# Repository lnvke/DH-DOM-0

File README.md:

# navball
A compact display showing horizon, heading, and ground speed. Makes use of the BMI270 inertial measuring unit (IMU) to provide orientation, velocity, and acceleration data to display on screen.

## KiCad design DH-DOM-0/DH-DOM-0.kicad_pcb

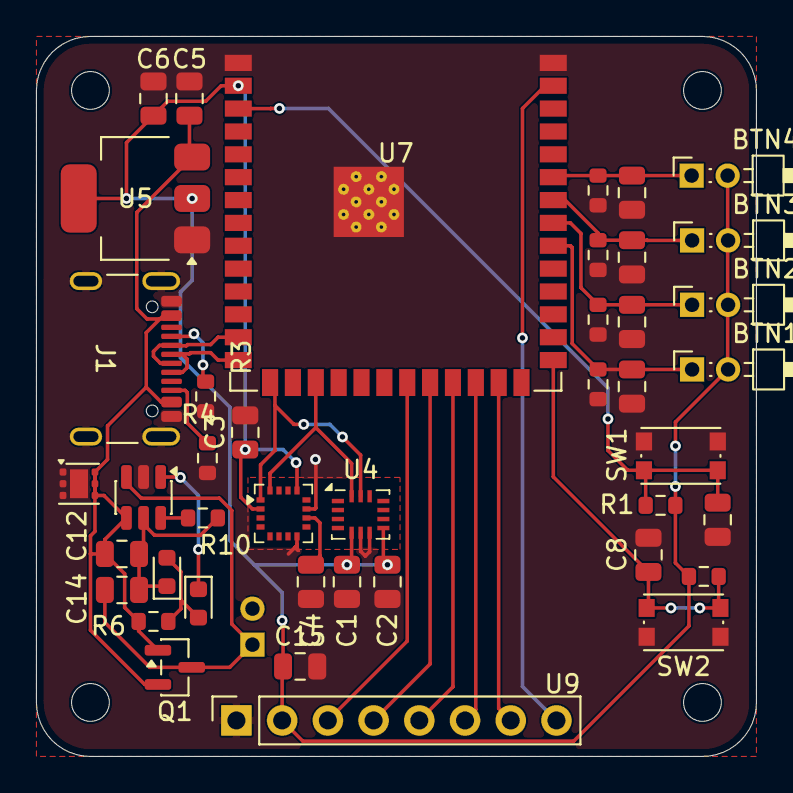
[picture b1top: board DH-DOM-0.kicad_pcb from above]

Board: 2 copper layers, 40.0 x 40.0 mm, 47 parts (1 on the bottom side), 27 nets.

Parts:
BTN1, BTN2, BTN3, BTN4: SW_Push; PinHeader_2x01_P2.00mm_Horizontal
C1, C2, C3, C7, C8, C9, C10, C11, C13, C15: 100n; C_0805_2012Metric
C4, C5, C6, C12: 10u; C_0805_2012Metric
C14: 4.7u; C_0805_2012Metric
D1, D2: LED; LED_0603_1608Metric
J1: USB_C_Receptacle_USB2.0_14P; USB_C_Receptacle_GCT_USB4105-xx-A_16P_TopMnt_Horizontal
J2: Conn_01x02; PinHeader_2x01_P2.00mm_Vertical
MH1, MH2, MH3, MH4: MountingHole_2.1mm
Q1: FDN340P; SOT-23
R1, R2: 1K; R_0603_1608Metric
R3, R4: 5.1k; R_0603_1608Metric
R5, R7, R8, R9: 10k; R_0603_1608Metric
R6: 1k; R_0603_1608Metric
R10: 10K; R_0603_1608Metric
SW1: RST; SW_Push_1P1T_NO_CK_KMR2
SW2: BOOT; SW_Push_1P1T_NO_CK_KMR2
U3: MMC5983MA; LGA-16_3x3mm_P0.5mm
U4: BMI270; Bosch_LGA-14_3x2.5mm_P0.5mm
U5: NCP1117-3.3_SOT223; SOT-223-3_TabPin2
U6: TVS1400DRV; WSON-6-1EP_2x2mm_P0.65mm_EP1x1.6mm
U7: ESP32-S3-WROOM-1-N4R8; ESP32-S3-WROOM-1
U8: TP4057; TSOT-23-6
U9: ST7789; PinSocket_1x08_P2.54mm_Vertical

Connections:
+3V3: BTN1.2, BTN2.2, BTN3.2, BTN4.2, C1.1, C2.1, C3.1, C6.1, C15.1, R1.1, R2.1, U3.2 (VDD), U3.13 (VDDIO), U4.5 (VDDI0), U4.8 (VDD), U5.2 (VO), U7.2 (3V3), U9.2
+5V: C5.1, C12.1, J1.A4 (VBUS), J1.A9 (VBUS), J1.B4 (VBUS), J1.B9 (VBUS), Q1.1 (G), Q1.2 (S), R6.2, U5.3 (VI), U6.4 (IN), U6.5 (IN), U6.6 (IN), U8.4 (V_{CC})
/BACKLIGHT: U7.39 (IO1), U9.8
/BAT+: C14.1, J2.1, Q1.3 (D), U8.3 (BAT)
/BTN1: BTN1.1, C9.1, R5.1, U7.32 (IO39)
/BTN2: BTN2.1, C10.1, R7.1, U7.33 (IO40)
/BTN3: BTN3.1, C11.1, R8.1, U7.34 (IO41)
/BTN4: BTN4.1, C13.1, R9.1, U7.35 (IO42)
/D+: J1.A6 (D+), J1.B6 (D+), U7.14 (USB_D+)
/D-: J1.A7 (D-), J1.B7 (D-), U7.13 (USB_D-)
/D/C: U7.24 (IO47), U9.6
/MOSI: U7.22 (IO14), U9.4
/RESET: U7.23 (IO21), U9.5
/SCL: U3.1 (SCx), U4.13 (SCx), U7.15 (IO3)
/SCLK: U7.21 (IO13), U9.3
/SDA: U3.16 (MOSI/SDA), U4.14 (SDx), U7.17 (IO9)
/SS: U7.25 (IO48), U9.7
GND: C1.2, C2.2, C3.2, C4.2, C5.2, C6.2, C7.2, C8.2, C9.2, C10.2, C11.2, C13.2, C15.2, J1.A1 (GND), J1.A12 (GND), J1.B1 (GND), J1.B12 (GND), J1.SH (SHIELD), J2.2, R3.2, R4.2, R5.2, R7.2, R8.2, R9.2, SW1.1, SW2.1, U3.8 (GND), U3.11 (GND), U4.6 (GNDI0), U4.7 (GND), U5.1 (GND), U6.1 (GND), U6.2 (GND), U6.3 (GND), U6.7 (GND), U7.1 (GND), U7.40 (GND), U7.41 (GND), U8.2 (GND), U9.1
unnamed: D1.2 (A), D2.2 (A), R6.1
unnamed: C12.2, C14.2, D1.1 (K), R10.2, U8.5 (STDBY)
unnamed: D2.1 (K), U8.1 (~CHRG)
unnamed: J1.A5 (CC1), R3.1
unnamed: J1.B5 (CC2), R4.1
unnamed: C4.1, U3.10 (CAP)
unnamed: C7.1, R1.2, SW1.2, U7.3 (EN)
unnamed: C8.1, R2.2, SW2.2, U7.27 (IO0)
unnamed: R10.1, U8.6 (PROG)

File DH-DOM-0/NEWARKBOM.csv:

"Reference","Qty","Value","DNP","Exclude from BOM","Exclude from Board","Footprint","Datasheet"
"BTN1,BTN2,BTN3,BTN4","4","SW_Push","","","","Connector_PinHeader_2.00mm:PinHeader_2x01_P2.00mm_Horizontal",""
"C1,C2,C3,C7,C8,C9,C10,C11,C13,C14","10","100n","","","","Capacitor_SMD:C_0805_2012Metric",""
"C4,C5,C6,C12","4","10u","","","","Capacitor_SMD:C_0805_2012Metric",""
"C15","1","4.7u","","","","Capacitor_SMD:C_0805_2012Metric",""
"D1,D2","2","LED","","","","LED_SMD:LED_0603_1608Metric",""
"J1","1","USB_C_Receptacle_USB2.0_14P","","","","Connector_USB:USB_C_Receptacle_GCT_USB4105-xx-A_16P_TopMnt_Horizontal","https://www.usb.org/sites/default/files/documents/usb_type-c.zip"
"J2","1","Conn_01x02","","","","Connector_PinHeader_2.00mm:PinHeader_2x01_P2.00mm_Vertical",""
"Q1","1","FDN340P","","","","Package_TO_SOT_SMD:SOT-23","https://www.onsemi.com/pub/Collateral/FDN340P-D.PDF"
"R1,R2","2","1K","","","","Resistor_SMD:R_0603_1608Metric",""
"R3,R4","2","5.1k","","","","Resistor_SMD:R_0603_1608Metric",""
"R5,R7,R8,R9","4","10k","","","","Resistor_SMD:R_0603_1608Metric",""
"R6","1","1k","","","","Resistor_SMD:R_0603_1608Metric",""
"R10","1","10K","","","","Resistor_SMD:R_0603_1608Metric",""
"SW1","1","RST","","","","Button_Switch_SMD:SW_Push_1P1T_NO_CK_KMR2",""
"SW2","1","BOOT","","","","Button_Switch_SMD:SW_Push_1P1T_NO_CK_KMR2",""
"U3","1","MMC5983MA","","","","Package_LGA:LGA-16_3x3mm_P0.5mm",""
"U4","1","BMI270","","","","Package_LGA:Bosch_LGA-14_3x2.5mm_P0.5mm","https://www.bosch-sensortec.com/media/boschsensortec/downloa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"
"U5","1","NCP1117-3.3_SOT223","","","","Package_TO_SOT_SMD:SOT-223-3_TabPin2","http://www.onsemi.com/pub_link/Collateral/NCP1117-D.PDF"
"U6","1","TVS1400DRV","","","","Package_SON:WSON-6-1EP_2x2mm_P0.65mm_EP1x1.6mm","http://www.ti.com/lit/ds/symlink/tvs1400.pdf"
"U7","1","ESP32-S3-WROOM-1-N4R8","","","","RF_Module:ESP32-S3-WROOM-1","https://www.espressif.com/sites/default/files/documentation/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"
"U8","1","TP4057","","","","Package_TO_SOT_SMD:TSOT-23-6","http://toppwr.com/uploadfile/file/20230304/640302a47b738.pdf"
"U9","1","ST7789","","","","Connector_PinSocket_2.54mm:PinSocket_1x08_P2.54mm_Vertical",""

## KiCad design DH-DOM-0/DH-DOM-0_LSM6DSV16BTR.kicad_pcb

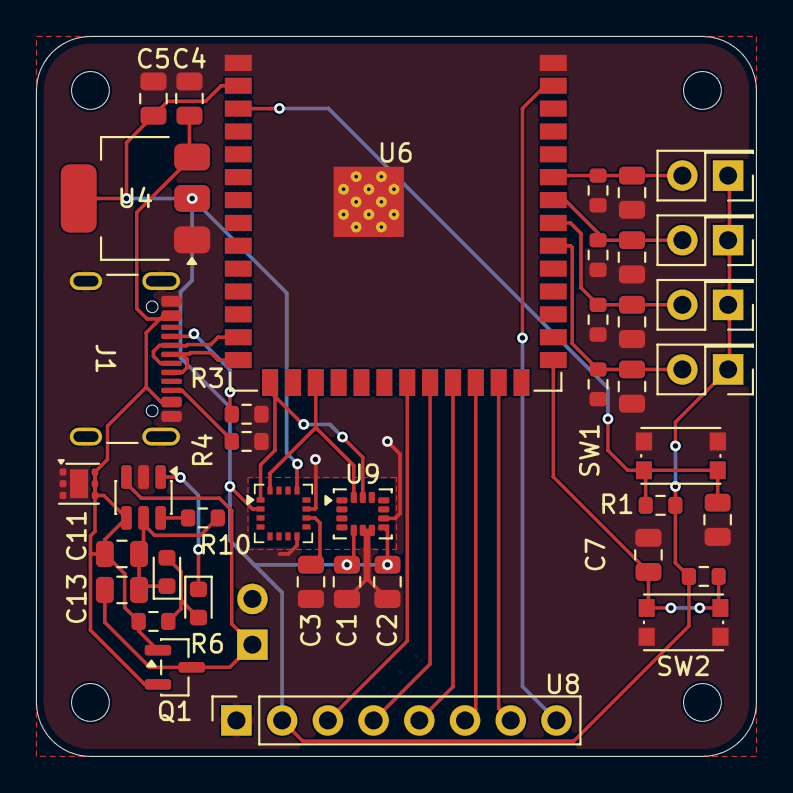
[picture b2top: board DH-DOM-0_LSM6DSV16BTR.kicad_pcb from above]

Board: 2 copper layers, 40.0 x 40.0 mm, 45 parts (1 on the bottom side), 27 nets.

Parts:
BTN1, BTN2, BTN3, BTN4: SW_Push; PinHeader_2x01_P2.54mm_Vertical
C1, C2, C6, C7, C8, C9, C10, C12: 100n; C_0805_2012Metric
C3, C4, C5, C11: 10u; C_0805_2012Metric
C13: 4.7u; C_0805_2012Metric
D1, D2: LED; LED_0603_1608Metric
J1: USB_C_Receptacle_USB2.0_14P; USB_C_Receptacle_GCT_USB4105-xx-A_16P_TopMnt_Horizontal
J2: Conn_01x02; PinHeader_2x01_P2.54mm_Vertical
MH1, MH2, MH3, MH4: MountingHole_2.1mm
Q1: FDN340P; SOT-23
R1, R2: 1K; R_0603_1608Metric
R3, R4: 5.1k; R_0603_1608Metric
R5, R7, R8, R9: 10k; R_0603_1608Metric
R6: 1k; R_0603_1608Metric
R10: 10K; R_0603_1608Metric
SW1: RST; SW_Push_1P1T_NO_CK_KMR2
SW2: BOOT; SW_Push_1P1T_NO_CK_KMR2
U2: MMC5983MA; LGA-16_3x3mm_P0.5mm
U4: NCP1117-3.3_SOT223; SOT-223-3_TabPin2
U5: TVS1400DRV; WSON-6-1EP_2x2mm_P0.65mm_EP1x1.6mm
U6: ESP32-S3-WROOM-1-N4R8; ESP32-S3-WROOM-1
U7: TP4057; TSOT-23-6
U8: ST7789; PinSocket_1x08_P2.54mm_Vertical
U9: LSM6DSV16BTR; LGA-14_3x2.5mm_P0.5mm_LayoutBorder3x4y

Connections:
+3V3: BTN1.1, BTN2.1, BTN3.1, BTN4.1, C1.1, C2.1, C5.1, R1.1, R2.1, U2.2 (VDD), U2.13 (VDDIO), U4.2 (VO), U6.2 (3V3), U8.2, U9.5 (VDDIO), U9.8 (VDD)
+5V: C4.1, C11.1, J1.A4 (VBUS), J1.A9 (VBUS), J1.B4 (VBUS), J1.B9 (VBUS), Q1.1 (G), Q1.2 (S), R6.2, U4.3 (VI), U5.4 (IN), U5.5 (IN), U5.6 (IN), U7.4 (V_{CC})
/BACKLIGHT: U6.39 (IO1), U8.8
/BAT+: C13.1, J2.1, Q1.3 (D), U7.3 (BAT)
/BTN1: BTN1.2, C8.1, R5.1, U6.32 (IO39)
/BTN2: BTN2.2, C9.1, R7.1, U6.33 (IO40)
/BTN3: BTN3.2, C10.1, R8.1, U6.34 (IO41)
/BTN4: BTN4.2, C12.1, R9.1, U6.35 (IO42)
/D+: J1.A6 (D+), J1.B6 (D+), U6.14 (USB_D+)
/D-: J1.A7 (D-), J1.B7 (D-), U6.13 (USB_D-)
/D/C: U6.24 (IO47), U8.6
/MOSI: U6.22 (IO14), U8.4
/RESET: U6.23 (IO21), U8.5
/SCL: U2.1 (SCx), U6.15 (IO3), U9.13 (SCL)
/SCLK: U6.21 (IO13), U8.3
/SDA: U2.16 (MOSI/SDA), U6.17 (IO9), U9.14 (SDA)
/SS: U6.25 (IO48), U8.7
GND: C1.2, C2.2, C3.2, C4.2, C5.2, C6.2, C7.2, C8.2, C9.2, C10.2, C12.2, J1.A1 (GND), J1.A12 (GND), J1.B1 (GND), J1.B12 (GND), J1.SH (SHIELD), J2.2, R3.2, R4.2, R5.2, R7.2, R8.2, R9.2, SW1.1, SW2.1, U2.8 (GND), U2.11 (GND), U4.1 (GND), U5.1 (GND), U5.2 (GND), U5.3 (GND), U5.7 (GND), U6.1 (GND), U6.40 (GND), U6.41 (GND), U7.2 (GND), U8.1, U9.6 (RES), U9.7 (GND), U9.9 (RES)
unnamed: D1.2 (A), D2.2 (A), R6.1
unnamed: C11.2, C13.2, D1.1 (K), R10.2, U7.5 (STDBY)
unnamed: D2.1 (K), U7.1 (~CHRG)
unnamed: J1.A5 (CC1), R3.1
unnamed: J1.B5 (CC2), R4.1
unnamed: C3.1, U2.10 (CAP)
unnamed: C6.1, R1.2, SW1.2, U6.3 (EN)
unnamed: C7.1, R2.2, SW2.2, U6.27 (IO0)
unnamed: R10.1, U7.6 (PROG)

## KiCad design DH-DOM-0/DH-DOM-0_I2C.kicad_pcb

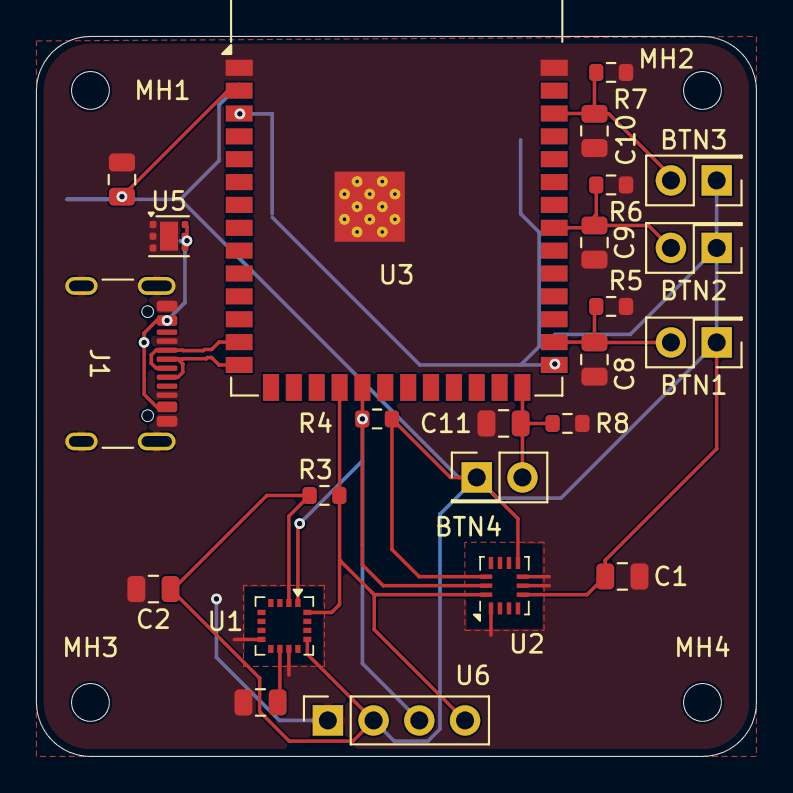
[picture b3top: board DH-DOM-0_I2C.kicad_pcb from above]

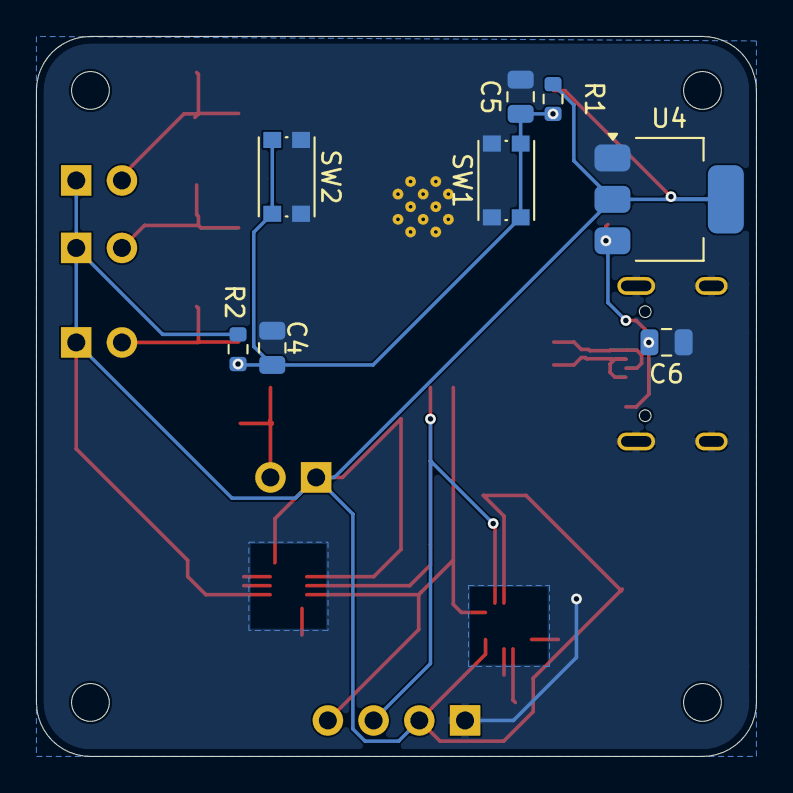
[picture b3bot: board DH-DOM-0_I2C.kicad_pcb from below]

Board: 2 copper layers, 40.0 x 40.0 mm, 36 parts (8 on the bottom side), 13 nets.

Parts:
BTN1, BTN2, BTN3, BTN4: SW_Push; PinHeader_2x01_P2.54mm_Vertical
C1, C2, C4, C5, C8, C9, C10, C11: 100n; C_0805_2012Metric
C3, C6, C7: 10u; C_0805_2012Metric
J1: USB_C_Receptacle_USB2.0_14P; USB_C_Receptacle_GCT_USB4105-xx-A_16P_TopMnt_Horizontal
MH1, MH2, MH3, MH4: MountingHole_2.1mm
R1, R2: 1K; R_0603_1608Metric
R3, R4: 2.7K; R_0603_1608Metric
R5, R6, R7, R8: 10k; R_0603_1608Metric
SW1: RST; SW_Push_1P1T_NO_CK_KMR2
SW2: BOOT; SW_Push_1P1T_NO_CK_KMR2
U1: MMC5983MA; LGA-16_3x3mm_P0.5mm
U2: BMI270; Bosch_LGA-14_3x2.5mm_P0.5mm
U3: ESP32-S3-WROOM-1
U4: NCP1117-3.3_SOT223; SOT-223-3_TabPin2
U5: TVS1400DRV; WSON-6-1EP_2x2mm_P0.65mm_EP1x1.6mm
U6: SSD1306; PinSocket_1x04_P2.54mm_Vertical

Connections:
+3V3: BTN1.1, BTN2.1, BTN3.1, BTN4.1, C1.1, C2.1, C7.1, R1.1, R2.1, R3.1, R4.1, U1.2 (VDD), U1.13 (VDDIO), U2.5 (VDDI0), U2.8 (VDD), U2.12 (CSB), U3.2 (3V3), U4.2 (VO), U6.2
+5V: C6.1, J1.A4 (VBUS), J1.A9 (VBUS), J1.B4 (VBUS), J1.B9 (VBUS), U4.3 (VI), U5.4 (IN), U5.5 (IN), U5.6 (IN)
/BTN1: BTN1.2, C8.1, R5.1, U3.28 (IO35)
/BTN2: BTN2.2, C9.1, R6.1, U3.33 (IO40)
/BTN3: BTN3.2, C10.1, R7.1, U3.38 (IO2)
/BTN4: BTN4.2, C11.1, R8.1, U3.26 (IO45)
/D+: J1.A6 (D+), J1.B6 (D+), U3.14 (USB_D+)
/D-: J1.A7 (D-), J1.B7 (D-), U3.13 (USB_D-)
/SCL: R4.2, U1.1 (SCx), U2.13 (SCx), U3.19 (IO11), U6.3
/SDA: R3.2, U1.16 (SDA/SDI), U2.14 (SDx), U3.18 (IO10), U6.4
GND: C1.2, C2.2, C3.2, C4.2, C5.2, C6.2, C7.2, C8.2, C9.2, C10.2, C11.2, J1.A1 (GND), J1.A5 (CC1), J1.A12 (GND), J1.B1 (GND), J1.B5 (CC2), J1.B12 (GND), J1.SH (SHIELD), R5.2, R6.2, R7.2, R8.2, SW1.1, SW2.1, U1.8 (GND), U1.11 (GND), U2.1 (SDO), U2.6 (GNDI0), U2.7 (GND), U3.1 (GND), U3.40 (GND), U3.41 (GND), U4.1 (GND), U5.1 (GND), U5.2 (GND), U5.3 (GND), U5.7 (GND), U6.1
unnamed: C3.1, U1.10 (CAP)
unnamed: C4.1, C5.1, R1.2, R2.2, SW1.2, SW2.2, U3.3 (EN), U3.27 (IO0)

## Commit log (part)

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2026-04-20 Add files via upload
    started
2026-04-20 BMI270 symbol
2026-04-20 BMI270 symbol real
2026-04-21 Finished Bare Schematic
2026-04-21 test
2026-04-21 schematic update
    + schematic finished
    + fixed symbols
    + finished assignment of footprints for most components
    - still need button footprints
2026-04-21 fix
    fixed wiring error with UI
2026-04-21 edit
    + changed ssd1306 from normal footprint to through hole component for later prototyping and more flexible wiring in final
    - ERC errors
2026-04-21 pcb finish
2026-04-21 fix
    + no more relevant DRC errors
2026-04-21 fix
    + fixed ground plane
    - excluded DRC errors for through hole clearance violation for ESP32 gnd pad and USB pins
2026-04-21 added bom
    new bom
2026-04-22 new model
    added model for cad
2026-04-22 added step
    lower quality step file added for easier cad
2026-04-25 bom added
2026-04-25 fix
    bom
2026-04-27 edit
    new imu, new footprint, edited schematic, new pcb, old one saved as I2C
2026-04-27 edit
    pcb almost done, last decoupling capacitors and screen routing left. also needs drc check
2026-04-27 fix
    replaced lost data from crash
2026-04-27 fix
    re-did lost data
2026-04-28 fix
    done i think
2026-04-28 edit
    finish
2026-04-28 fix
    new routing for imus, changed SPI to single bus instead of using more
2026-04-29 edit
    added charging
2026-04-30 fix
    added indicator LEDs to charging circuit
2026-04-30 edit
    schematic
2026-04-30 edit
    removed extra volt reg
2026-04-30 edit
    pcb done
2026-05-01 organization
    put old i2c versions into separate folder
2026-05-02 edit
    i dont remember
2026-05-03 edit
    battery protection
2026-05-04 edit
    added diode again? idk something happened
2026-05-04 fix
    rerouted misrouted boot settings pins
2026-05-05 edit
    added bmi270 backup just in case LSM6DSOXTR goes out of stock (only 2 left)
    might switch to another imu idk, ESP32 I2C library is a must.
    Currently building BOM
2026-05-05 edit
    extra backup MEMS/IMU because digikey keeps running out
2026-05-05 save
    save
2026-05-05 edit
    separate versions for different IMUs, same footprint but traces have miniscule differences.
2026-05-06 edit
    added MEMS/IMU specific board variants
2026-05-06 bom update
    using bmi270 MAYBE. i still like the LSM6DSV16BTR better
2026-05-06 edit
    git push sum idk rlly
2026-05-07 edit
    put everything on top layer 3v3 cap
2026-05-07 edit
    new step files
2026-05-08 edit
    new header pitch
2026-05-08 edit
    dont remember
2026-05-09 edit
    forgot lowkey
2026-05-09 edit
    dont know either
2026-05-14 eduiyuyt
    durrrrrrrr
2026-05-15 edit
    new bom new supplier newark maybe AVNET
